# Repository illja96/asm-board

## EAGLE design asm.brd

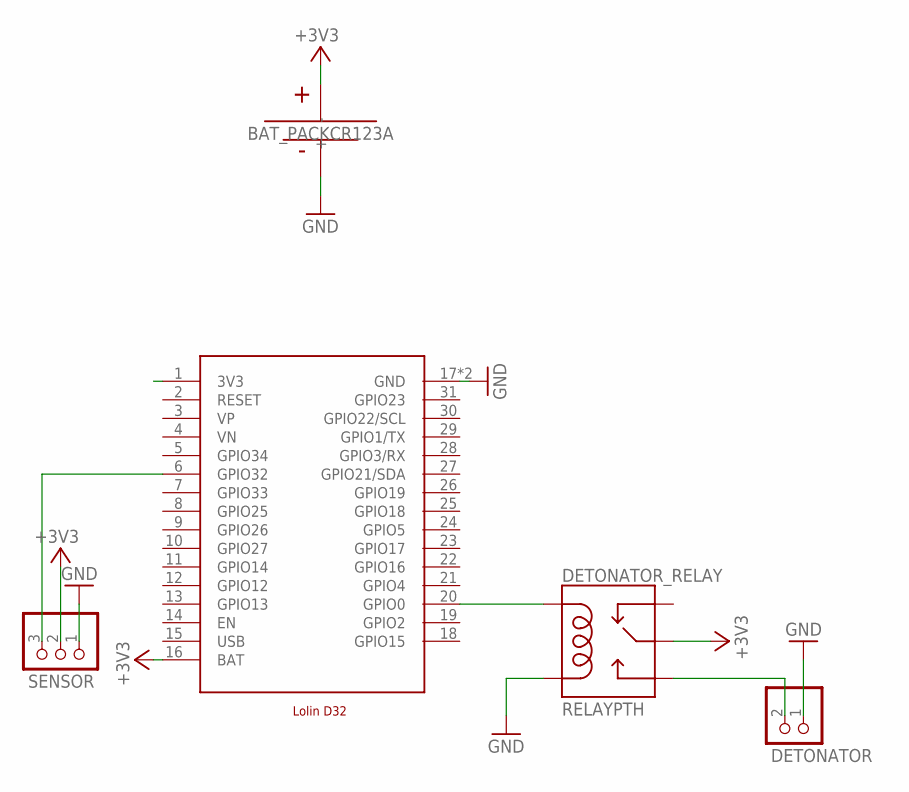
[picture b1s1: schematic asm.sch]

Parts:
CR123A: BAT_PACKCR123A; BH123A
DETONATOR: PINHD-1X2; 1X02
DETONATOR_RELAY: RELAYPTH; SRD-05VDC-SL-C
ESP32: LOLIND32
SENSOR: PINHD-1X3; 1X03

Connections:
+3V3: CR123A.+, DETONATOR_RELAY.SWCOMMON, ESP32.16 (BAT), SENSOR.2
GND: CR123A.-, DETONATOR.1, DETONATOR_RELAY.COIL0, ESP32.17 (GND), ESP32.32 (GND), SENSOR.1
unnamed: ESP32.6 (GPIO32), SENSOR.3
unnamed: DETONATOR_RELAY.COIL1, ESP32.20 (GPIO0)
unnamed: DETONATOR.2, DETONATOR_RELAY.SWOPEN
USB: ESP32.15 (USB)

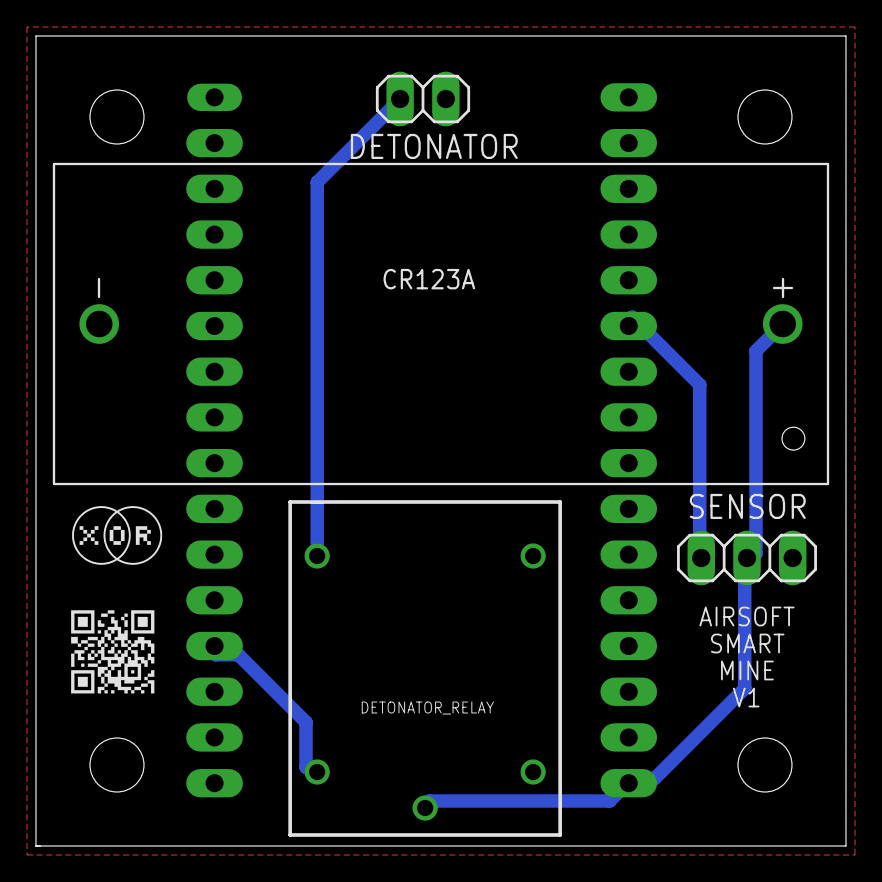
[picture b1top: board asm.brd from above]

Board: 2 copper layers, 45.0 x 45.0 mm, 5 parts (1 on the bottom side), 5 nets.

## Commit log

2021-02-04 Add v1 schemas
